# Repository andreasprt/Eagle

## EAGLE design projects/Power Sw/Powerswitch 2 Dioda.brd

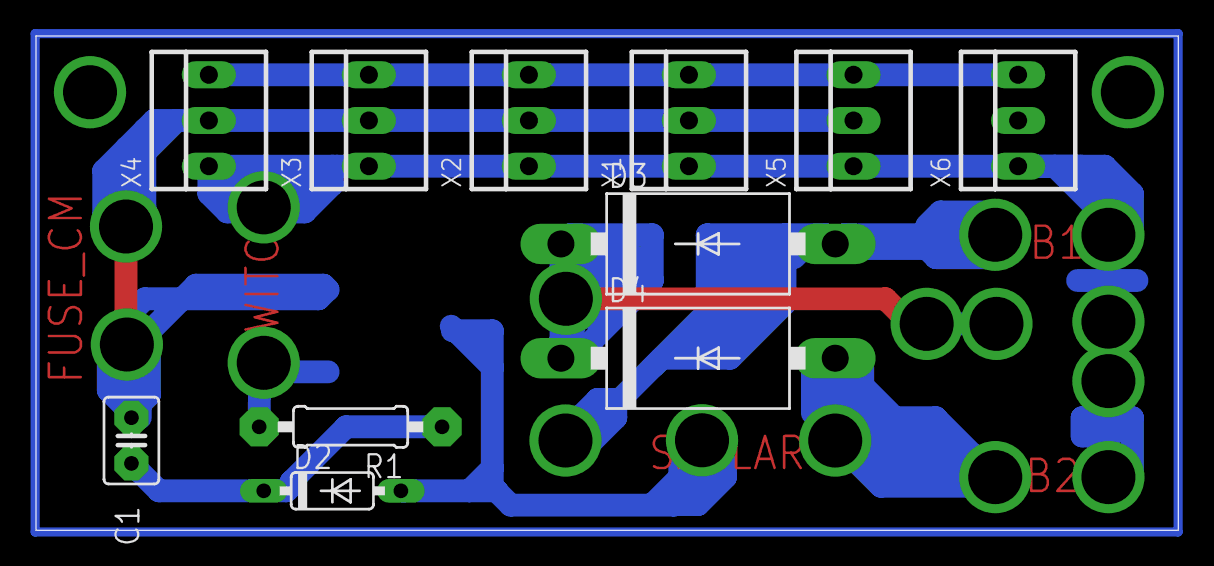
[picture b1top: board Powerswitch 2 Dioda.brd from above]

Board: 2 copper layers, 63.5 x 27.5 mm, 12 parts (1 on the bottom side), 7 nets.

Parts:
C1: C025-030X050
D2: 1N4148DO35-7; DO35-7
D3, D4: 1N5400; DO201-15
Q1: 35A/25V/8.5mΩ; DPAK
R1: 0207/10
X1, X2, X3, X4, X5, X6: 22-23-2031

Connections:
DATA: X1.3, X2.3, X3.3, X4.3, X5.3, X6.3
GND: X1.1, X2.1, X3.1, X4.1, X5.1, X6.1
unnamed: C1.2, D2.C, R1.1
PC: D3.C, D4.C
SWITCH: Q1.1, R1.2
VIN: D2.A, Q1.4
VMOTOR: C1.1, Q1.3, X1.2, X2.2, X3.2, X4.2, X5.2

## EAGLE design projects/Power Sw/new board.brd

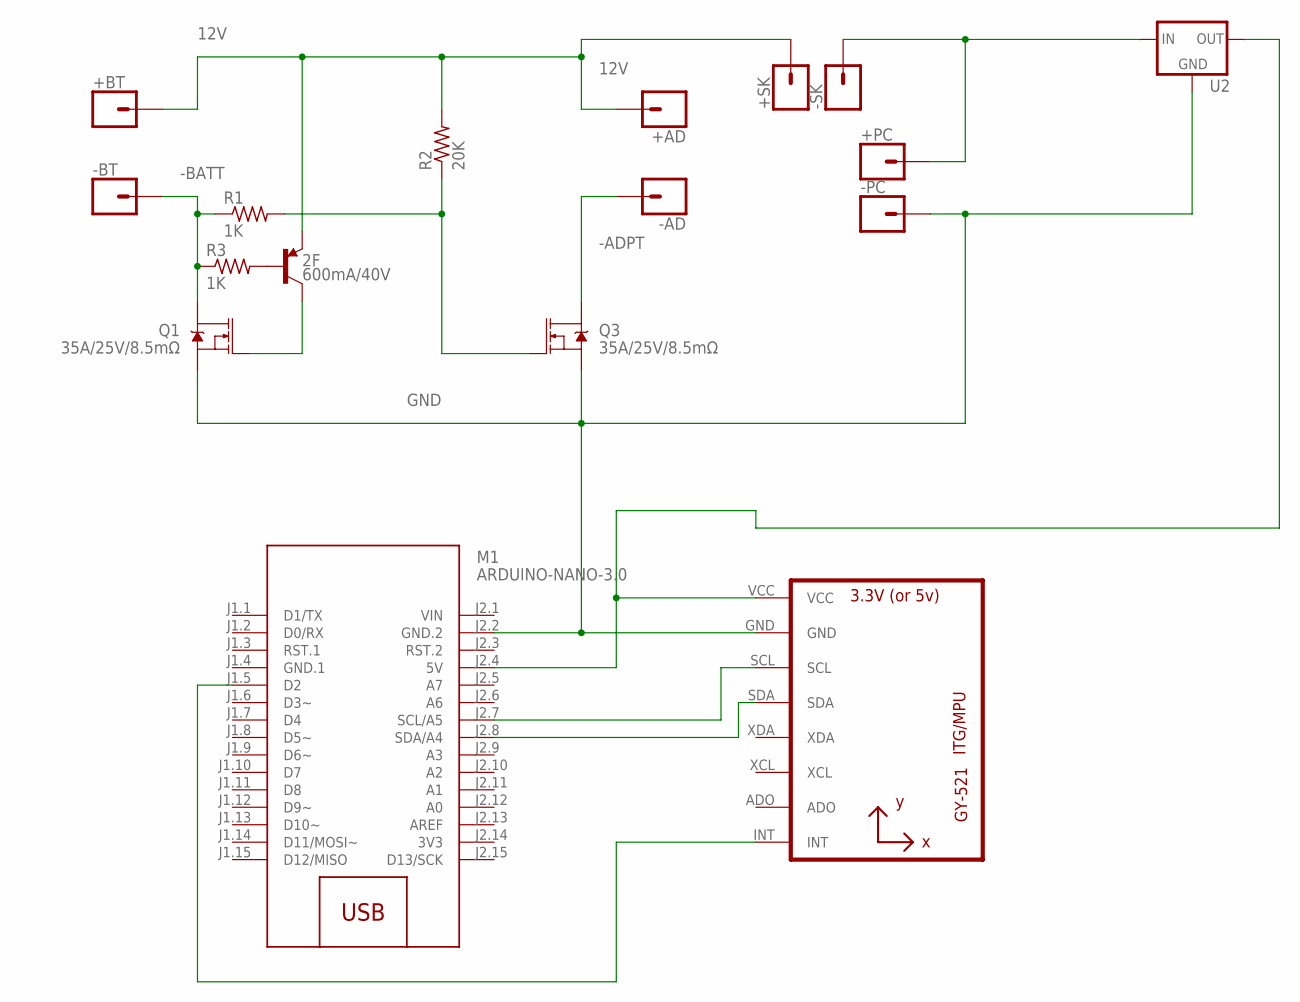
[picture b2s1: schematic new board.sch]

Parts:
2F: 600mA/40V; SOT23-3
+AD: CONN_01PTH_2MM; 1X01_2MM
+BT: CONN_01PTH_2MM; 1X01_2MM
+PC: CONN_01PTH_2MM; 1X01_2MM
+SK: CONN_01PTH_2MM; 1X01_2MM
-AD: CONN_01PTH_2MM; 1X01_2MM
-BT: CONN_01PTH_2MM; 1X01_2MM
-PC: CONN_01PTH_2MM; 1X01_2MM
-SK: CONN_01PTH_2MM; 1X01_2MM
M1: ARDUINO-NANO-3.0
Q1, Q3: 35A/25V/8.5mΩ; DPAK
R1, R3: 1K; M1206
R2: 20K; M1206
U1: GY-521MPU6050; GY-521
U2: +12v; TO-252

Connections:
3V3: M1.J2.14 (3V3)
12V: 2F.2 (E), +AD.1, +BT.1, +SK.1, R2.2
-ADPT: -AD.1, Q3.4 (D)
-BATT: -BT.1, Q1.4 (D), R1.1, R3.1
GND: -PC.1, M1.J2.2 (GND.2), Q1.3 (S), Q3.3 (S), U1.GND, U2.3 (GND)
GND.1: M1.J1.4 (GND.1)
unnamed: 2F.3 (C), Q1.1 (G)
unnamed: +PC.1, -SK.1, U2.1 (IN)
unnamed: Q3.1 (G), R1.2, R2.1
unnamed: M1.J2.4 (5V), U1.VCC, U2.2 (OUT)
unnamed: M1.J2.8 (SDA/A4), U1.SDA
unnamed: M1.J2.7 (SCL/A5), U1.SCL
unnamed: M1.J1.5 (D2), U1.INT
unnamed: 2F.1 (B), R3.2
VIN: M1.J2.1 (VIN)

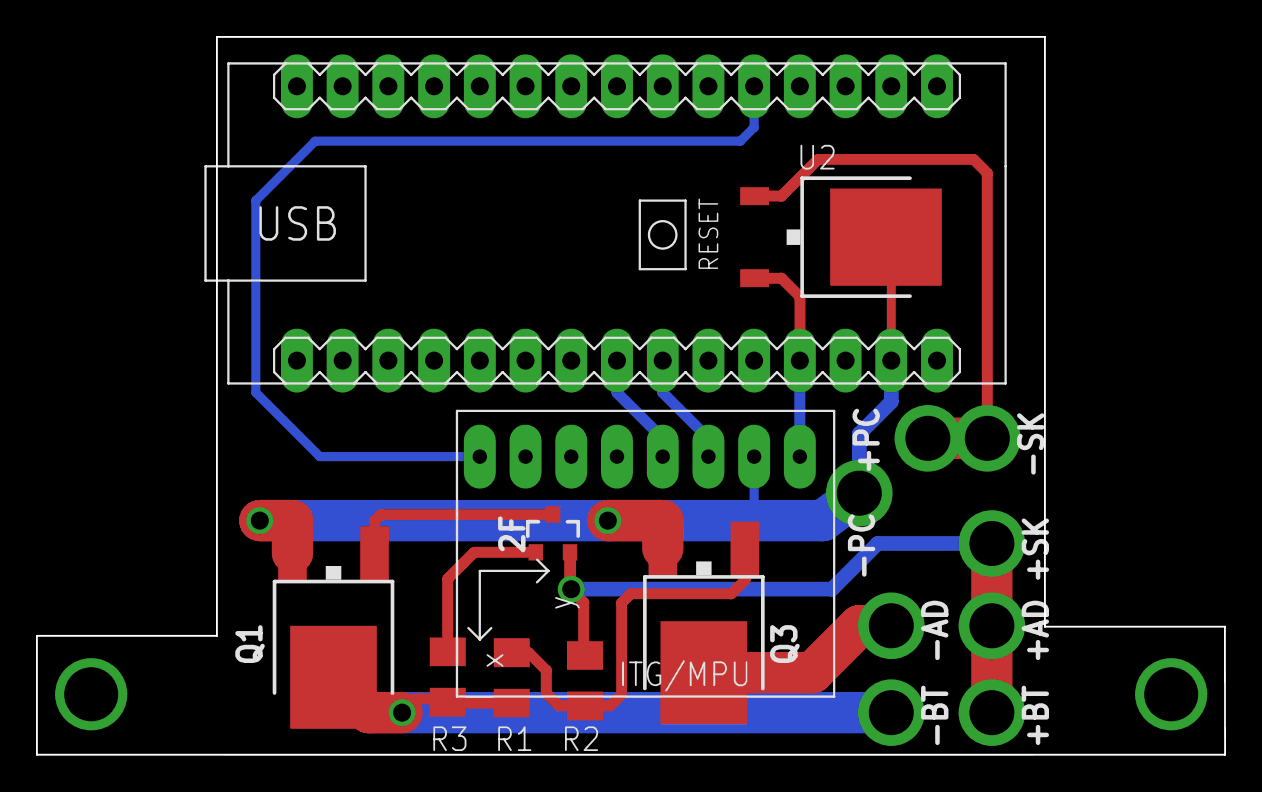
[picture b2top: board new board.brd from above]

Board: 2 copper layers, 66.0 x 39.9 mm, 17 parts (0 on the bottom side), 12 nets.

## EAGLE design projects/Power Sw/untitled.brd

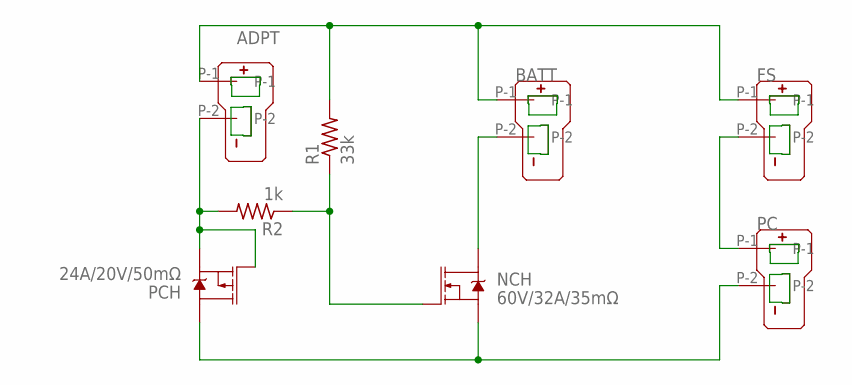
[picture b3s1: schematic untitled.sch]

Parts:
ADPT: T-PLUG_CONNECTOR; T_PLUG_CONNECTOR
BATT: T-PLUG_CONNECTOR; T_PLUG_CONNECTOR
FS: T-PLUG_CONNECTOR; T_PLUG_CONNECTOR
NCH: 60V/32A/35mΩ; TO220V
PC: T-PLUG_CONNECTOR; T_PLUG_CONNECTOR
PCH: 24A/20V/50mΩ; TO220V
R1: 33k; 0411/15
R2: 1k; 0411/15

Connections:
GND: NCH.3 (S), PC.P-2, PCH.2 (D)
unnamed: NCH.1 (G), R1.1, R2.1
unnamed: ADPT.P-2, PCH.1 (G), PCH.3 (S), R2.2
unnamed: BATT.P-2, NCH.2 (D)
unnamed: ADPT.P-1, BATT.P-1, FS.P-1, R1.2
unnamed: FS.P-2, PC.P-1

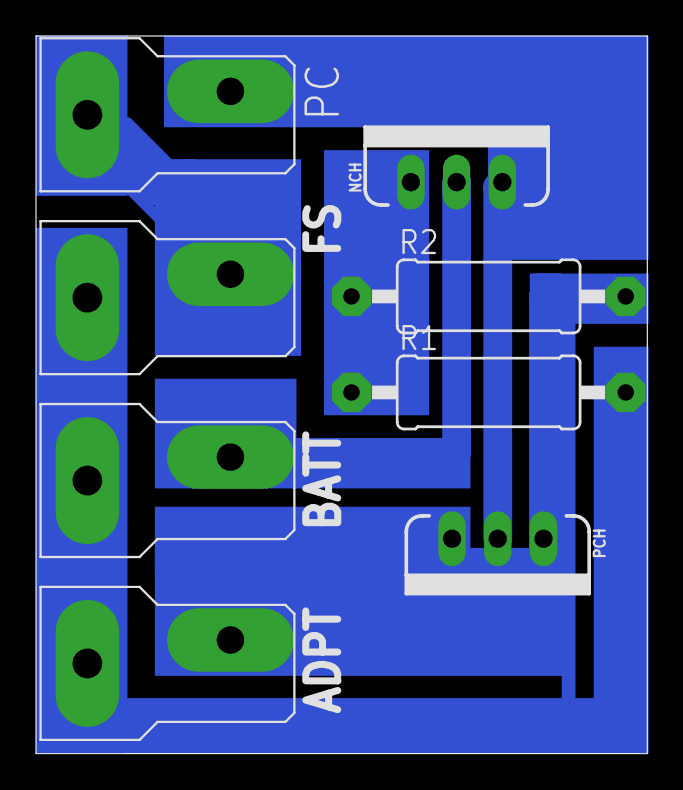
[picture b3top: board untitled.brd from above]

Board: 2 copper layers, 34.0 x 39.9 mm, 8 parts (0 on the bottom side), 6 nets.

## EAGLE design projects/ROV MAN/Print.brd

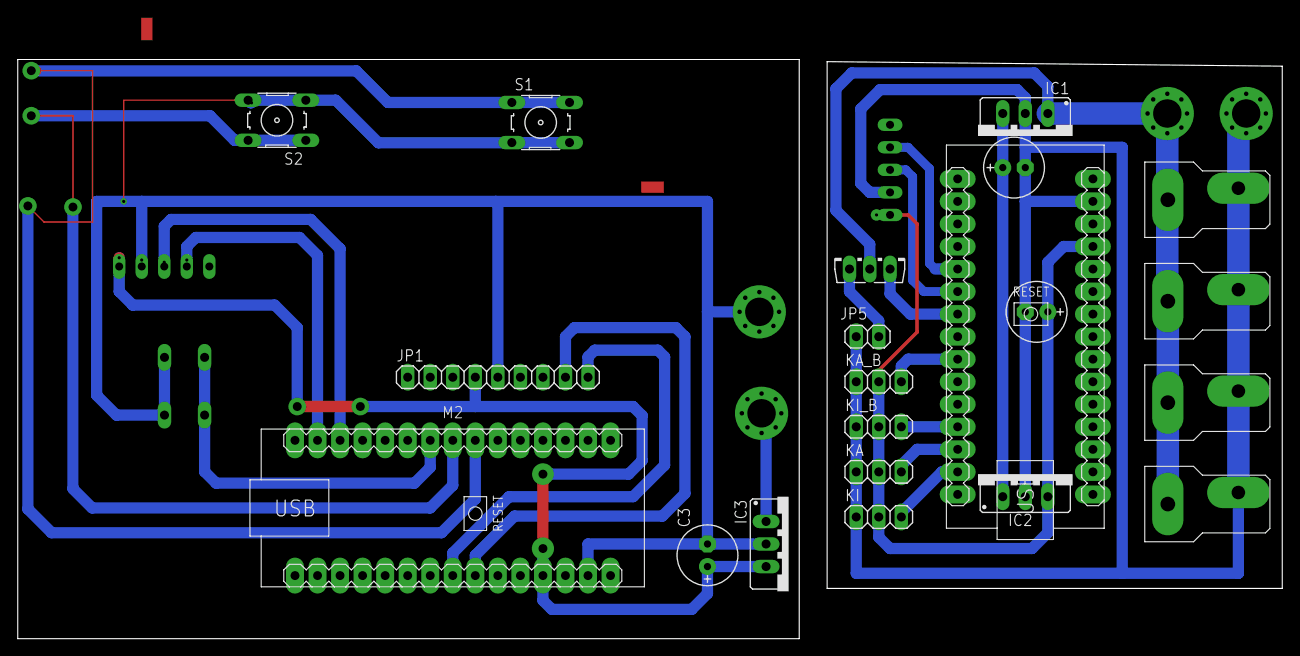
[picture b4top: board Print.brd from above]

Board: 2 copper layers, 142.5 x 65.3 mm, 28 parts (1 on the bottom side), 22 nets.

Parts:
C1, C2, C3: E2,5-7
H1, H2, H3, H4: 3MM_HOLE
IC1, IC2, IC3: 78XXS
JP1: 1X09
JP5: 1X02
KA: 1X03
KA_B: 1X03
KI: 1X03
KI_B: 1X03
M1, M2: ARDUINO-NANO-3.0
Q1: BD139; TO126AV
S1, S2, S3: B3F-10XX
U$1, U$2, U$3, U$4: T-PLUG_CONNECTOR; T_PLUG_CONNECTOR
U$5, U$6: HC-12_FOOTPRINT

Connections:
5V: C2.+, IC2.OUT, KA.2, KA_B.2, KI.2, KI_B.2, M1.J2.4, U$5.VCC
5V1: C3.+, IC3.OUT, JP1.4, M2.J2.4, U$6.VCC
10: M2.J1.13, U$6.RXD
11: M2.J1.14, U$6.TXD
A4: JP1.9, M2.J2.8
A5: JP1.8, M2.J2.7
GND: C1.-, C2.-, H2.P$1, H2.P$2, H2.P$3, H2.P$4, H2.P$5, H2.P$6, H2.P$7, H2.P$8, H2.P$9, IC1.GND, IC2.GND, JP5.2, KA.1, KA_B.1, KI.1, KI_B.1, M1.J2.2, U$1.P-2, U$2.P-2, U$3.P-2, U$4.P-2, U$5.GND
GND1: C3.-, H4.P$1, H4.P$2, H4.P$3, H4.P$4, H4.P$5, H4.P$6, H4.P$7, H4.P$8, H4.P$9, IC3.GND, JP1.5, M2.J2.2, S1.3, S1.4, S2.3, S2.4, S3.3, S3.4, U$6.GND
MAJU: M2.J1.7, S1.1, S1.2
MUNDUR: M2.J1.8, S2.1, S2.2
unnamed: C1.+, IC1.OUT, IC2.IN
unnamed: JP5.1, Q1.E
PIN_6: KA_B.3, M1.J1.9
PIN_9: KI_B.3, M1.J1.12
PIN_10: KA.3, M1.J1.13
PIN_11: KI.3, M1.J1.14
PUMP: M1.J1.7, Q1.B
PUMP1: M2.J1.9, S3.1, S3.2
RXD: M1.J1.6, U$5.RXD
TXD: M1.J1.5, U$5.TXD
VCC: H1.P$1, H1.P$2, H1.P$3, H1.P$4, H1.P$5, H1.P$6, H1.P$7, H1.P$8, H1.P$9, IC1.IN, Q1.C, U$1.P-1, U$2.P-1, U$3.P-1, U$4.P-1
VCC1: H3.P$1, H3.P$2, H3.P$3, H3.P$4, H3.P$5, H3.P$6, H3.P$7, H3.P$8, H3.P$9, IC3.IN

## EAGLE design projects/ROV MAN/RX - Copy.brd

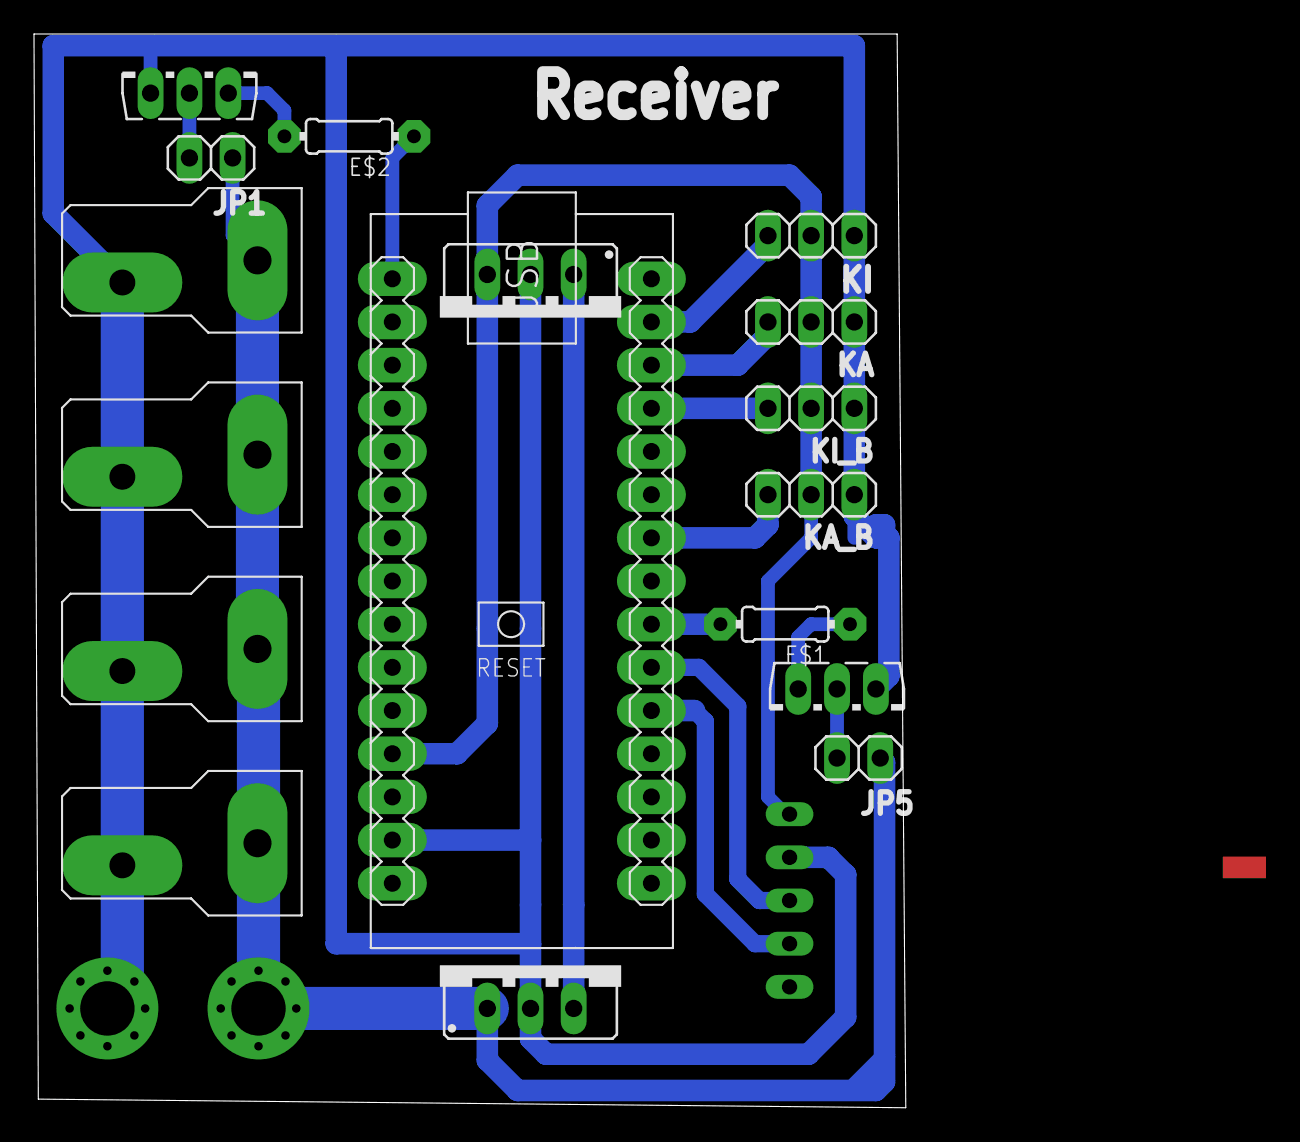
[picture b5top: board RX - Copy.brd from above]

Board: 2 copper layers, 51.3 x 63.2 mm, 20 parts (0 on the bottom side), 16 nets.

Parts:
E$1, E$2: 0204/7
H1, H2: 3MM_HOLE
IC1, IC2: 78XXS
JP1, JP5: 1X02
KA: 1X03
KA_B: 1X03
KI: 1X03
KI_B: 1X03
M1: ARDUINO-NANO-3.0
Q1, Q2: BD139; TO126AV
U$1, U$2, U$3, U$4: T-PLUG_CONNECTOR; T_PLUG_CONNECTOR
U$5: HC-12_FOOTPRINT

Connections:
5V: IC2.OUT, KA.2, KA_B.2, KI.2, KI_B.2, M1.J2.4, U$5.VCC
GND: H2.P$1, H2.P$2, H2.P$3, H2.P$4, H2.P$5, H2.P$6, H2.P$7, H2.P$8, H2.P$9, IC1.GND, IC2.GND, KA.1, KA_B.1, KI.1, KI_B.1, M1.J2.2, Q1.E, Q2.E, U$1.P-2, U$2.P-2, U$3.P-2, U$4.P-2, U$5.GND
unnamed: IC1.OUT, IC2.IN
PIN_6: KA_B.3, M1.J1.9
PIN_9: KI_B.3, M1.J1.12
PIN_10: KA.3, M1.J1.13
PIN_11: KI.3, M1.J1.14
RXD: M1.J1.6, U$5.RXD
S$1: JP5.1, Q1.C
S$2: E$1.2, M1.J1.7
S$3: E$1.1, Q1.B
S$4: JP1.1, Q2.C
S$5: E$2.2, Q2.B
S$6: E$2.1, M1.J2.15
TXD: M1.J1.5, U$5.TXD
VCC: H1.P$1, H1.P$2, H1.P$3, H1.P$4, H1.P$5, H1.P$6, H1.P$7, H1.P$8, H1.P$9, IC1.IN, JP1.2, JP5.2, U$1.P-1, U$2.P-1, U$3.P-1, U$4.P-1

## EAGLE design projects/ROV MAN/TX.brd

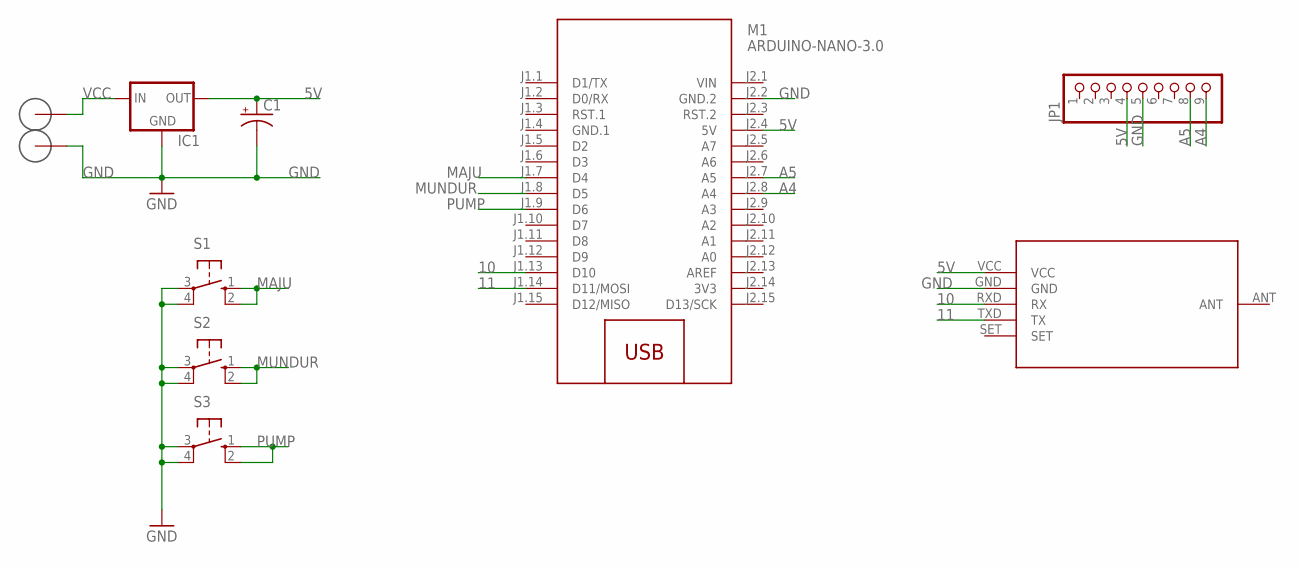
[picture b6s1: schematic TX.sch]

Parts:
C1: CPOL-USE2.5-7; E2,5-7
H1, H2: 3MM_HOLE
IC1: 78XXS
JP1: PINHD-1X9; 1X09
M1: ARDUINO-NANO-3.0
S1, S2, S3: 10-XX; B3F-10XX
U$1: HC-12_FOOTPRINT

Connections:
3V3: M1.J2.14 (3V3)
5V: C1.+, IC1.OUT, JP1.4, M1.J2.4 (5V), U$1.VCC
10: M1.J1.13 (D10), U$1.RXD (RX)
11: M1.J1.14 (D11/MOSI), U$1.TXD (TX)
A4: JP1.9, M1.J2.8 (A4)
A5: JP1.8, M1.J2.7 (A5)
GND: C1.-, H2.P$1, H2.P$2, H2.P$3, H2.P$4, H2.P$5, H2.P$6, H2.P$7, H2.P$8, H2.P$9, IC1.GND, JP1.5, M1.J2.2 (GND.2), S1.3, S1.4 (P1), S2.3, S2.4 (P1), S3.3, S3.4 (P1), U$1.GND
GND.1: M1.J1.4 (GND.1)
MAJU: M1.J1.7 (D4), S1.1 (S), S1.2 (S1)
MUNDUR: M1.J1.8 (D5), S2.1 (S), S2.2 (S1)
PUMP: M1.J1.9 (D6), S3.1 (S), S3.2 (S1)
VCC: H1.P$1, H1.P$2, H1.P$3, H1.P$4, H1.P$5, H1.P$6, H1.P$7, H1.P$8, H1.P$9, IC1.IN
VIN: M1.J2.1 (VIN)

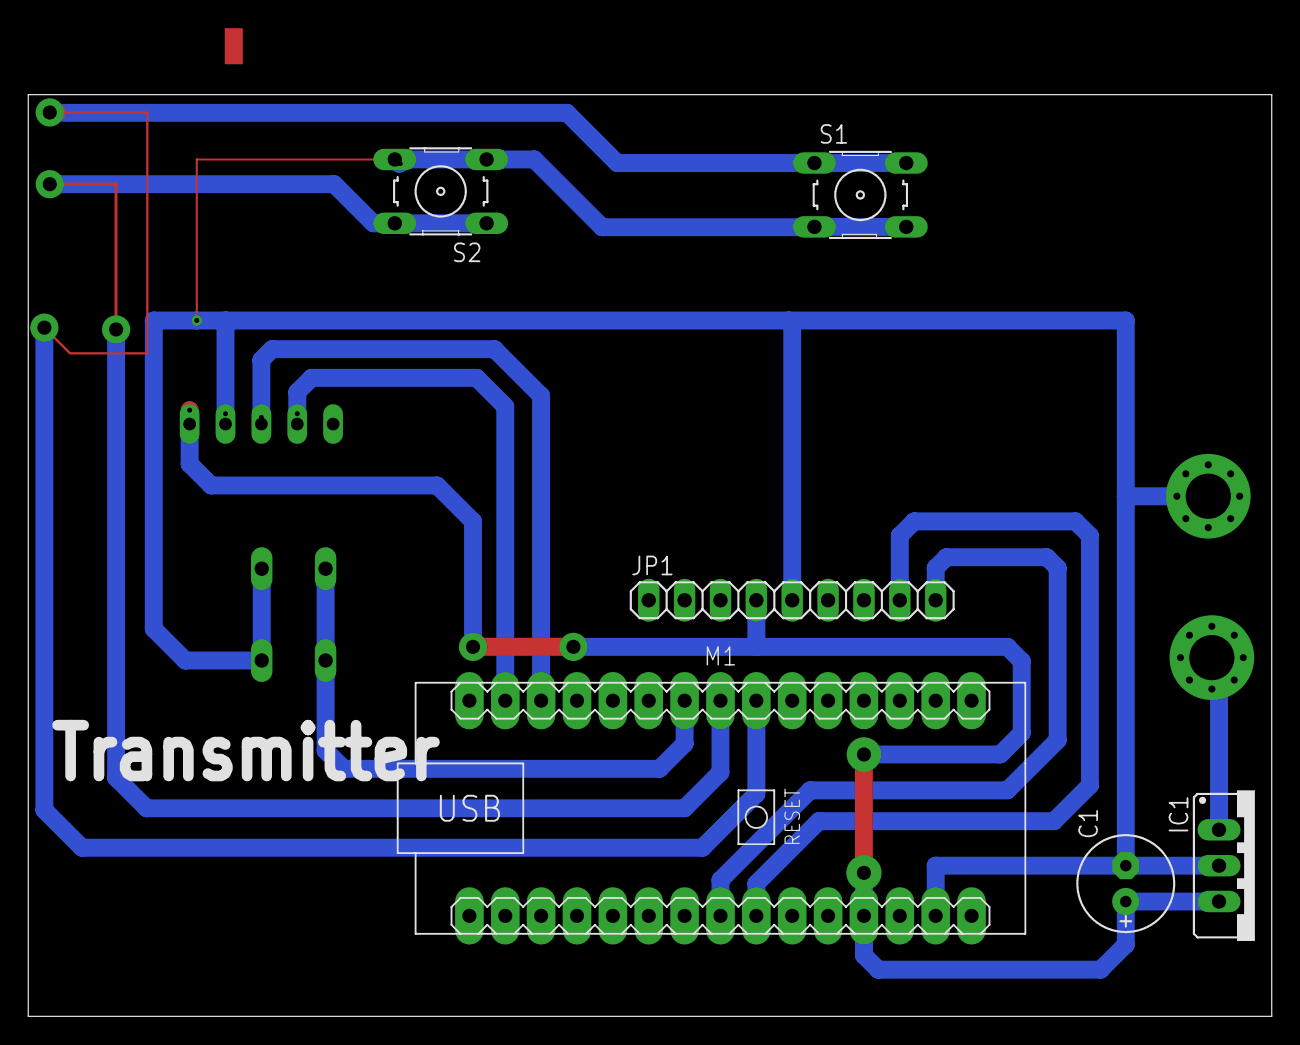
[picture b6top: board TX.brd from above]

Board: 2 copper layers, 88.1 x 65.3 mm, 10 parts (1 on the bottom side), 10 nets.

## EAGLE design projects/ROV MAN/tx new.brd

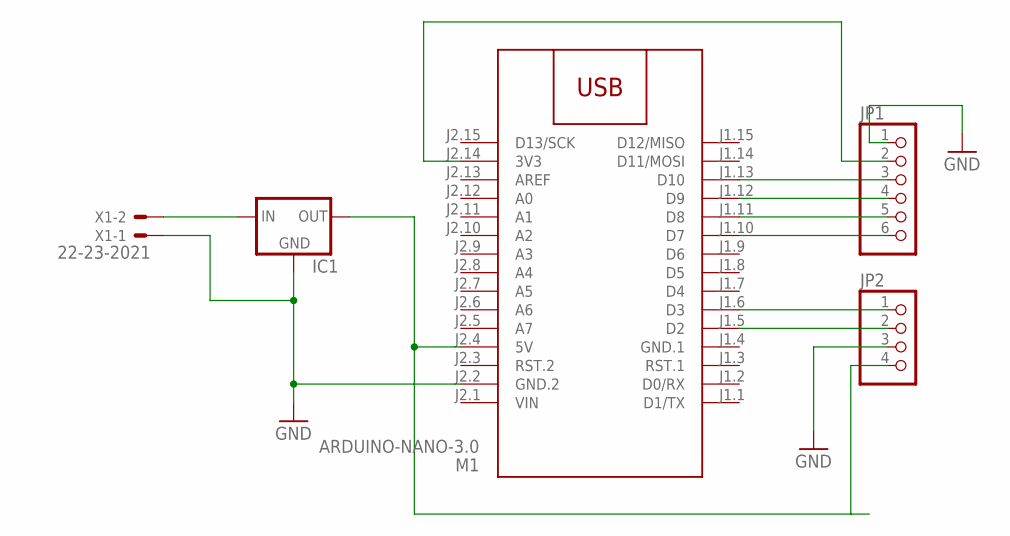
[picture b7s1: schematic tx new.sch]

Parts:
IC1: 78XXS
JP1: PINHD-1X6; 1X06
JP2: PINHD-1X4; 1X04
M1: ARDUINO-NANO-3.0
X1: 22-23-2021

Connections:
GND: IC1.GND, JP1.1, JP2.3, M1.J2.2 (GND.2), X1.1
GND.1: M1.J1.4 (GND.1)
unnamed: IC1.IN, X1.2
unnamed: JP2.1, M1.J1.6 (D3)
unnamed: IC1.OUT, JP2.4, M1.J2.4 (5V)
unnamed: JP1.2, M1.J2.14 (3V3)
unnamed: JP1.3, M1.J1.13 (D10)
unnamed: JP1.4, M1.J1.12 (D9)
unnamed: JP1.5, M1.J1.11 (D8)
unnamed: JP1.6, M1.J1.10 (D7)
unnamed: JP2.2, M1.J1.5 (D2)
VIN: M1.J2.1 (VIN)

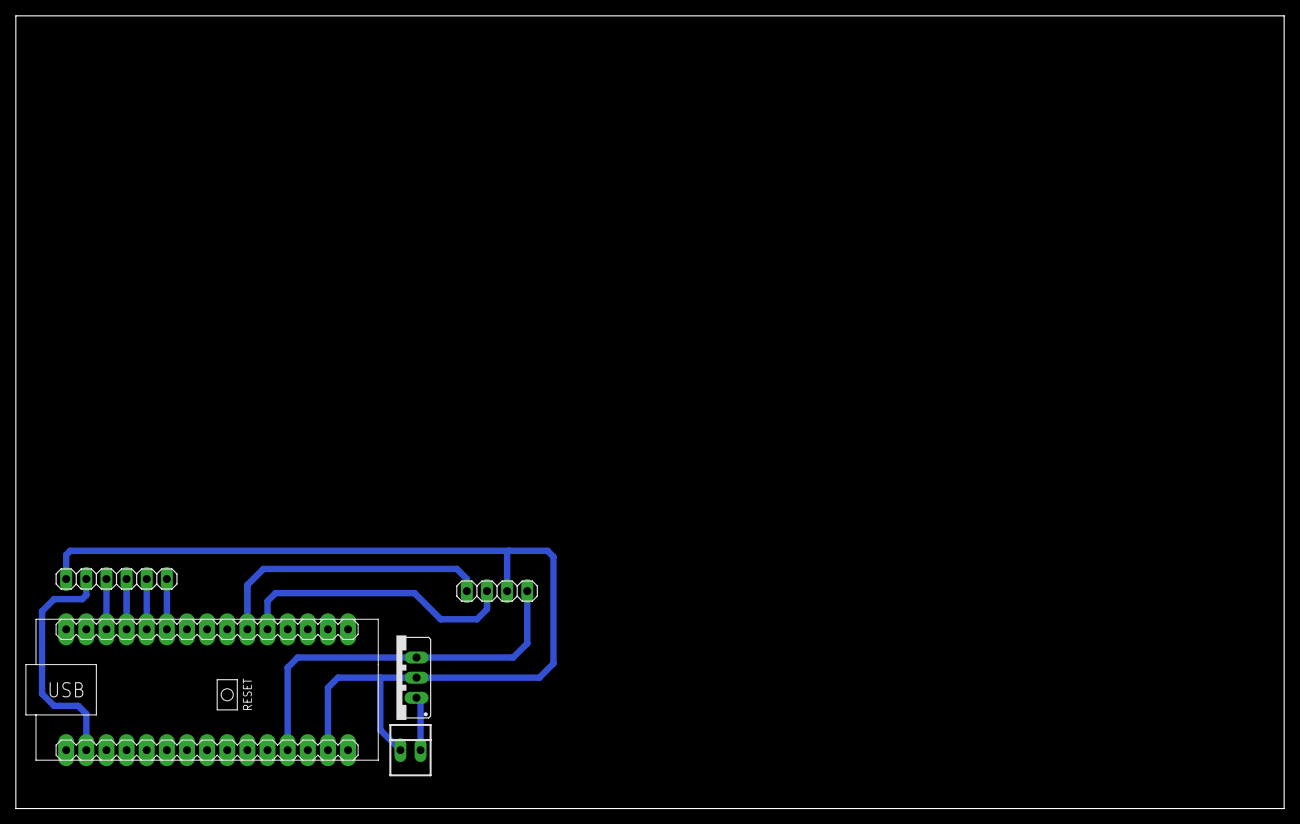
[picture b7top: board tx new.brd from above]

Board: 2 copper layers, 160.0 x 100.0 mm, 5 parts (0 on the bottom side), 10 nets.

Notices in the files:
parts and their libraries:
SparkFun-DiscreteSemi: Licensing: Creative Commons ShareAlike 4.0 International - https://creativecommons.org/licenses/by-sa/4.0
diy-modules: Released under the Creative Commons Attribution 4.0 International License: http://creativecommons.org/licenses/by/4.0
